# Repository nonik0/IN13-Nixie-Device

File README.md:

# IN13 Nixie Device

## Overview

This Nixie project is a continutation of the same spirit of most of my earlier Nixie projects: take an existing Nixie device, house it in a clean, well-built metal case, and maybe do a few addtions or modifications along the way. For me, the magic of Nixie tubes lies in their soft, ghostly glow—subtle, warm, and inviting. A simple, high-quality enclosure helps keep the attention where it belongs: on the Nixie itself.

Over the years, I’ve owned a few different Nixie thermometers, but they all came in acrylic cases. Aside from being acrylic, they were also bulky compared to the slim IN-13 tube and also used LED edge-lit acrylic to indicate temperature ranges. I don’t hate edge-lit acrylic on principle, but pairing that aesthetic with the aesthetic of Nixie tubes feels like a cardinal sin to me. I know there’s a huge market for flashy Nixie clocks with rainbow LEDs and effects, and plenty of people enjoy that style, but it’s just not for me. In my house, there’s a Nixie device in every room—and not a single RGB LED in sight. That’s been a personal rule for a while now.

At some point while browsing other Nixie projects, my mental levee broke and I had to start this project. TODO prototype? I started by finding a case I liked and sized well with an IN-13 tube, and worked back from that. My challenge for this was creating relatively cramped single sided PCB custom made for the case I had chosen, and this project is the result! and I dove into building this. I started by picking out a metal case I liked that fit the IN-13 well, and worked backward from there. My main challenge for this project was designing a compact, single-sided PCB tailored specifically to the dimensions of the enclosure I had chosen, and what you see here is the result!

inspiration:
https://yager.io/vumeter/vu.html
https://www.tindie.com/products/eclipsevl/in-13-bargraph-nixie-tube-with-driver-and-dc-dc/

## Hardware
The hardware is designed in KiCad 8.0, and all design files are included in the [hardware/kicad8.0](hardware/kicad8.0) directory.

The main hardware components are:
- IN-13 Nixie Tube
- [Bud Industries Aluminum Enclosure](https://www.budind.com/product/nema-ip-rated-boxes/an-a-series-style-a-aluminum-enclosure/an-1311-2)
- ESP32-C6 Mini
- TODO

## Firmware

TODO

## Images

TODO

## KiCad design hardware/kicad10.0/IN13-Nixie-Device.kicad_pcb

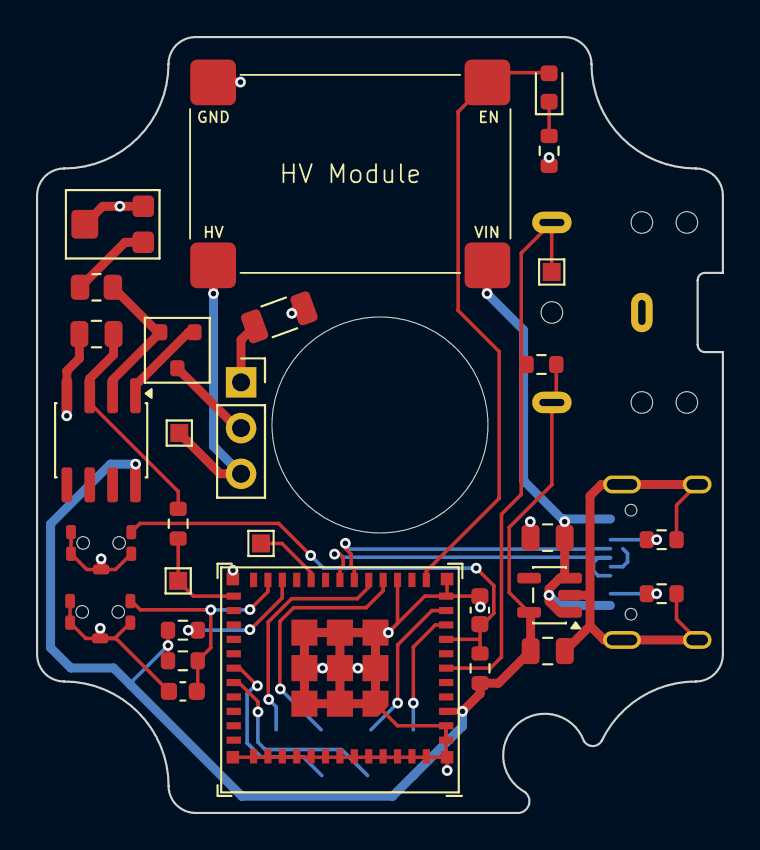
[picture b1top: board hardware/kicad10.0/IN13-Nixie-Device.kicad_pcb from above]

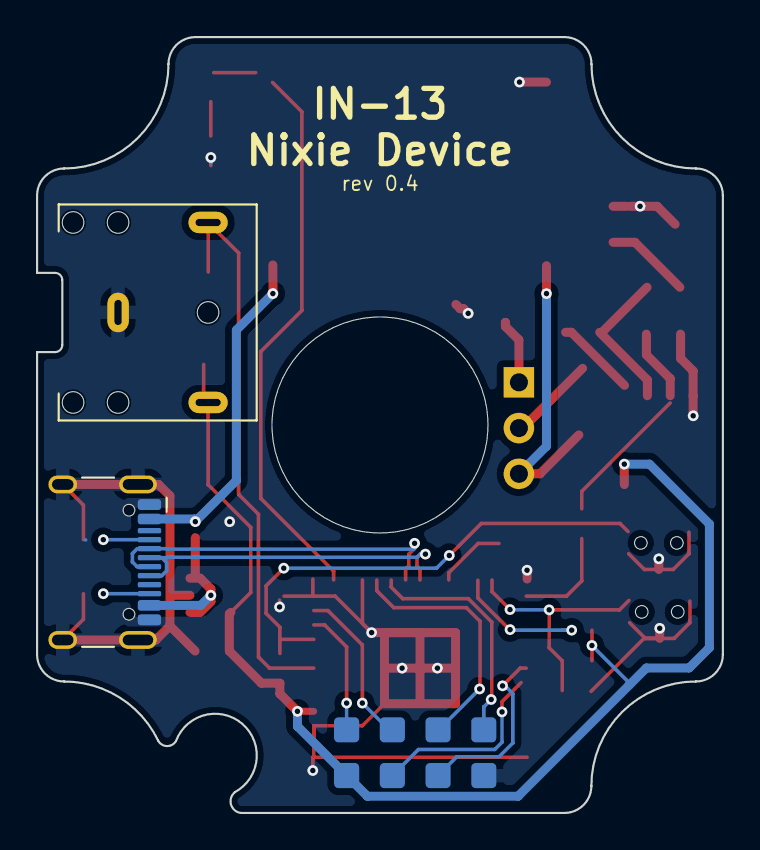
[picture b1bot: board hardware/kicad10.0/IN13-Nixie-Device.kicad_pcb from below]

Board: 2 copper layers, 38.1 x 43.1 mm, 33 parts (4 on the bottom side), 28 nets.

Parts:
C2: 100nF; C_0805_2012Metric
C3, C4: 1u; C_0603_1608Metric
C9, C12: 22u; C_0805_2012Metric
D3: LED; LED_0603_1608Metric
J1: PINHD_1x3_Female; PinSocket_1x03_P2.54mm_Vertical
J2: AudioJack3; Jack_3.5mm_CUI_SJ1-3523N_Horizontal_NoEdgeSilkscreen
J3: USB_C_Receptacle_USB2.0_16P; USB_C_Receptacle_HCTL_HC-TYPE-C-16P-01A
J4, J5: PINHD_1x4_Male; Pads_1x4_2.54mm
Q1: MMBTA42; SOT-23
R1: 220k; R_1206_3216Metric
R2, R3, R5, R6, R11: 10k; R_0603_1608Metric
R4: 330; R_0805_2012Metric
R12, R13: 5.1K; R_0603_1608Metric
R14: 220; R_0603_1608Metric
RV1: 2k; Potentiometer_Bourns_TC33X_Vertical
SW1, SW2: SW_Push; Mitsumi_SOFSeries_SMD_Button
TP1, TP2, TP4, TP5: TestPoint; TestPoint_Pad_1.0x1.0mm
U1: LM358; SOIC-8_3.9x4.9mm_P1.27mm
U2: ESP32-C6-MINI-1/U; ESP32-C6-MINI-1U
U4: AP2112K-3.3; SOT-23-5
U11: HV Module; AliExpress_HV_Module

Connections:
+3.3V: C12.1, J2.T, J4.1, R2.1, R5.2, R6.2, R11.1, U1.8 (V+), U2.3 (3V3), U4.5 (VOUT)
BOOT: C4.1, R6.1, SW2.1 (A), U2.23 (GPIO9)
D+: J3.A6 (D+), J3.B6 (D+), U2.18 (GPIO13/USB_D+)
D-: J3.A7 (D-), J3.B7 (D-), U2.17 (GPIO12/USB_D-)
EN: C3.1, R2.2, SW1.1 (A), U2.8 (EN/CHIP_PU)
GND: C2.2, C3.2, C4.2, C9.2, C12.2, J2.S, J3.A1 (GND), J3.A12 (GND), J3.B1 (GND), J3.B12 (GND), J3.SH (SHIELD), J4.4, R1.1, R12.2, R13.2, R14.1, RV1.2, RV1.3, SW1.2 (B), SW1.3 (GND), SW2.2 (B), SW2.3 (GND), U1.4 (V-), U2.1 (GND), U2.2 (GND), U2.11 (GND), U2.14 (GND), U2.36 (GND), U2.37 (GND), U2.38 (GND), U2.39 (GND), U2.40 (GND), U2.41 (GND), U2.42 (GND), U2.43 (GND), U2.44 (GND), U2.45 (GND), U2.46 (GND), U2.47 (GND), U2.48 (GND), U2.49 (GND), U2.50 (GND), U2.51 (GND), U2.52 (GND), U2.53 (GND), U4.2 (GND), U11.3 (Gnd)
HV: J1.3, TP2.1, U11.4 (Vout)
HVEN: D3.2 (A), U2.12 (GPIO0/ADC1_CH0/XTAL_32K_P), U11.2 (EN)
unnamed: D3.1 (K), R14.2
unnamed: J1.1, R1.2
unnamed: J3.A5 (CC1), R12.1
unnamed: J3.B5 (CC2), R13.1
unnamed: Q1.1 (B), U1.1
unnamed: J1.2, Q1.3 (C)
unnamed: Q1.2 (E), R4.1, U1.2 (-)
unnamed: R4.2, RV1.1
unnamed: C2.1, R3.1, U1.3 (+)
unnamed: R5.1, U2.22 (GPIO8)
unnamed: TP5.1 (1_1), U2.20 (GPIO15)
PWM: R3.2, TP1.1 (1_1), U2.25 (GPIO19)
RX: J4.3, U2.30 (U0RXD/GPIO17)
SIGNAL: J2.R, R11.2, TP4.1 (1_1), U2.6 (GPIO3/ADC1_CH3)
TCK: J5.3, U2.15 (MTCK/GPIO6/ADC1_CH6)
TDI: J5.2, U2.10 (MTDI/GPIO5/ADC1_CH5)
TDO: J5.4, U2.16 (MTDO/GPIO7)
TMS: J5.1, U2.9 (MTMS/GPIO4/ADC1_CH4)
TX: J4.2, U2.31 (U0TXD/GPIO16)
VBUS: C9.1, J3.A4 (VBUS), J3.A9 (VBUS), J3.B4 (VBUS), J3.B9 (VBUS), U4.1 (VIN), U4.3 (EN), U11.1 (Vin)

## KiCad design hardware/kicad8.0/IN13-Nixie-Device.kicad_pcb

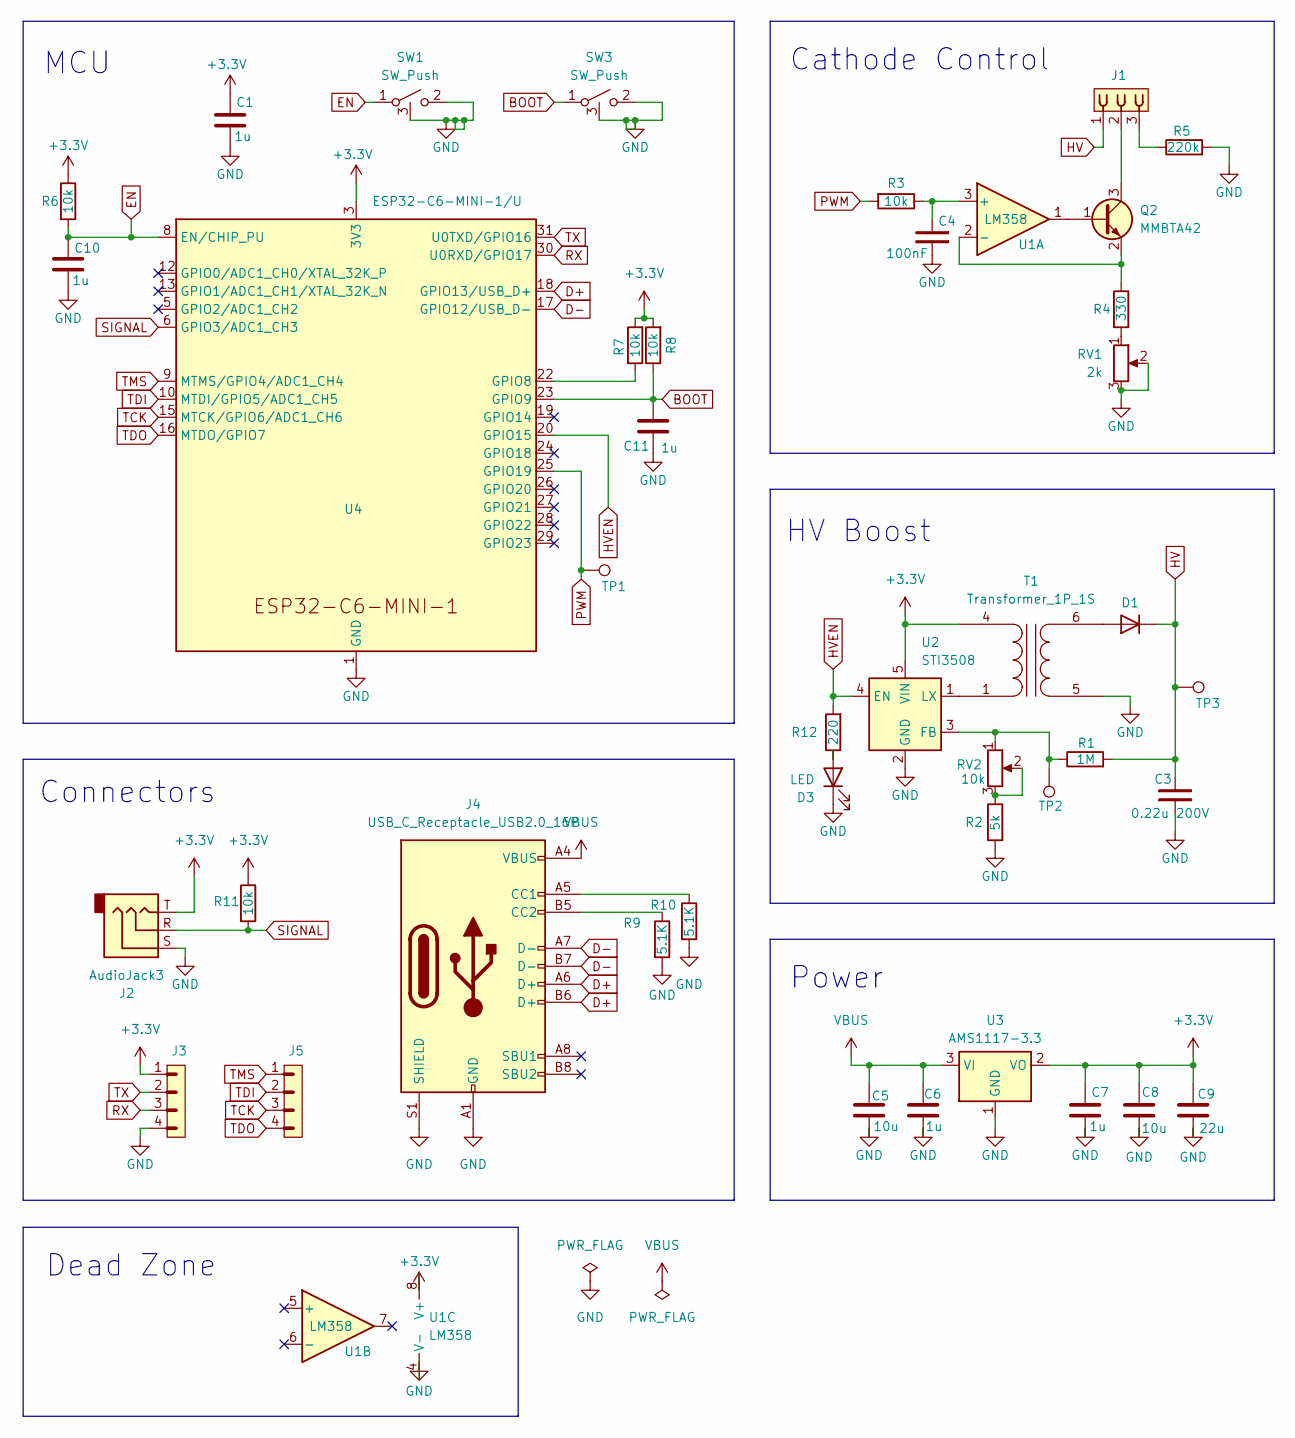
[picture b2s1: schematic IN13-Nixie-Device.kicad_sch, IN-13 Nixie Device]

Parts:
C1, C10, C11: 1u; C_0603_1608Metric
C3: 0.22u 200V; C_1210_3225Metric
C4: 100nF; C_0805_2012Metric
C5, C8: 10u; C_0805_2012Metric
C6, C7: 1u; C_0805_2012Metric
C9: 22u; C_0805_2012Metric
D1: US1G; D_SMA
D3: LED; LED_0603_1608Metric
J1: PINHD_1x3_Female; PinSocket_1x03_P2.54mm_Vertical
J2: AudioJack3; Jack_3.5mm_CUI_SJ1-3523N_Horizontal_NoEdgeSilkscreen
J3, J5: PINHD_1x4_Male; Pads_1x4_2.54mm
J4: USB_C_Receptacle_USB2.0_16P; USB_C_Receptacle_HCTL_HC-TYPE-C-16P-01A
Q2: MMBTA42; SOT-23
R1: 1M; R_0805_2012Metric
R2: 5k; R_0805_2012Metric
R3, R6, R7, R8, R11: 10k; R_0603_1608Metric
R4: 330; R_0805_2012Metric
R5: 220k; R_1206_3216Metric
R9, R10: 5.1K; R_0603_1608Metric
R12: 220; R_0603_1608Metric
RV1: 2k; Potentiometer_Bourns_TC33X_Vertical
RV2: 10k; Potentiometer_Bourns_TC33X_Vertical
SW1, SW3: SW_Push; Mitsumi_SOFSeries_SMD_Button
T1: Transformer_1P_1S; EE0504S
TP1, TP2, TP3: TestPoint; TestPoint_Pad_1.0x1.0mm
U1: LM358; SOIC-8_3.9x4.9mm_P1.27mm
U2: STI3508; SOT-23-6
U3: AMS1117-3.3; SOT-223-3_TabPin2
U4: ESP32-C6-MINI-1/U; ESP32-C6-MINI-1U

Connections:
+3.3V: C1.1, C7.1, C8.1, C9.1, J2.T, J3.1, R6.1, R7.2, R8.2, R11.1, T1.4 (AA), U1.8 (V+), U2.5 (VIN), U3.2 (VO), U4.3 (3V3)
BOOT: C11.1, R8.1, SW3.1 (A), U4.23 (GPIO9)
D+: J4.A6 (D+), J4.B6 (D+), U4.18 (GPIO13/USB_D+)
D-: J4.A7 (D-), J4.B7 (D-), U4.17 (GPIO12/USB_D-)
EN: C10.1, R6.2, SW1.1 (A), U4.8 (EN/CHIP_PU)
GND: C1.2, C3.1, C4.2, C5.2, C6.2, C7.2, C8.2, C9.2, C10.2, C11.2, D3.1 (K), J2.S, J3.4, J4.A1 (GND), J4.A12 (GND), J4.B1 (GND), J4.B12 (GND), J4.S1 (SHIELD), R2.2, R5.2, R9.2, R10.2, RV1.2, RV1.3, SW1.2 (B), SW1.3 (GND), SW3.2 (B), SW3.3 (GND), T1.5 (SA), U1.4 (V-), U2.2 (GND), U3.1 (GND), U4.1 (GND), U4.2 (GND), U4.11 (GND), U4.14 (GND), U4.36 (GND), U4.37 (GND), U4.38 (GND), U4.39 (GND), U4.40 (GND), U4.41 (GND), U4.42 (GND), U4.43 (GND), U4.44 (GND), U4.45 (GND), U4.46 (GND), U4.47 (GND), U4.48 (GND), U4.49 (GND), U4.50 (GND), U4.51 (GND), U4.52 (GND), U4.53 (GND)
HV: C3.2, D1.1 (K), J1.1, R1.2, TP3.1
HVEN: R12.2, U2.4 (EN), U4.20 (GPIO15)
unnamed: D1.2 (A), T1.6 (SB)
unnamed: D3.2 (A), R12.1
unnamed: J1.3, R5.1
unnamed: J4.A5 (CC1), R10.1
unnamed: J4.B5 (CC2), R9.1
unnamed: Q2.1 (B), U1.1
unnamed: J1.2, Q2.3 (C)
unnamed: Q2.2 (E), R4.1, U1.2 (-)
unnamed: R2.1, RV2.2, RV2.3
unnamed: R4.2, RV1.1
unnamed: T1.1 (AB), U2.1 (LX)
unnamed: C4.1, R3.1, U1.3 (+)
unnamed: R1.1, RV2.1, TP2.1, U2.3 (FB)
unnamed: R7.1, U4.22 (GPIO8)
PWM: R3.2, TP1.1, U4.25 (GPIO19)
RX: J3.3, U4.30 (U0RXD/GPIO17)
SIGNAL: J2.R, R11.2, U4.6 (GPIO3/ADC1_CH3)
TCK: J5.3, U4.15 (MTCK/GPIO6/ADC1_CH6)
TDI: J5.2, U4.10 (MTDI/GPIO5/ADC1_CH5)
TDO: J5.4, U4.16 (MTDO/GPIO7)
TMS: J5.1, U4.9 (MTMS/GPIO4/ADC1_CH4)
TX: J3.2, U4.31 (U0TXD/GPIO16)
VBUS: C5.1, C6.1, J4.A4 (VBUS), J4.A9 (VBUS), J4.B4 (VBUS), J4.B9 (VBUS), U3.3 (VI)

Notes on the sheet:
Cathode Control
HV Boost
Dead Zone
MCU
Connectors
Power

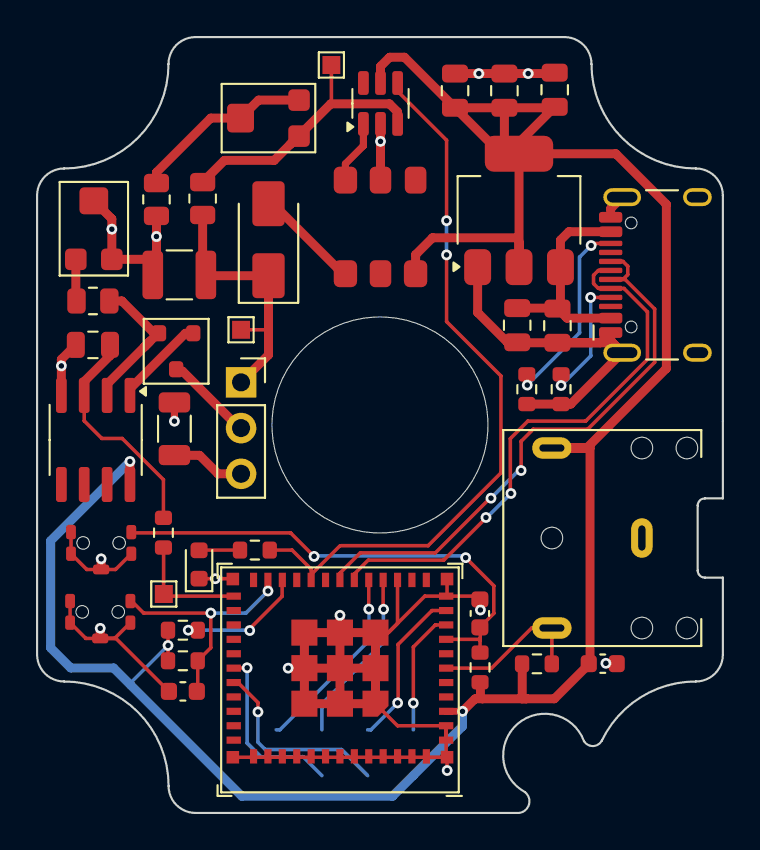
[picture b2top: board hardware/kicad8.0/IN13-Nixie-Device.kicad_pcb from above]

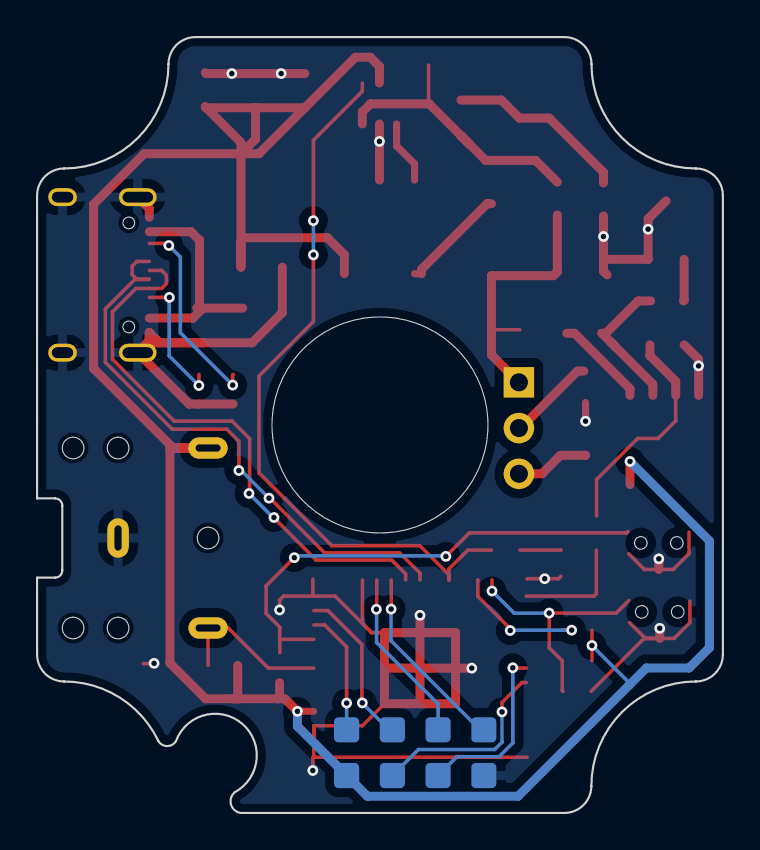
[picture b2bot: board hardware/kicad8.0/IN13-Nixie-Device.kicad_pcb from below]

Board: 2 copper layers, 38.1 x 43.1 mm, 42 parts (2 on the bottom side), 31 nets.

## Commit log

2025-02-07 initial commit, schematic in progress
2025-02-10 minor
2025-03-01 adding boilerplate rust esp project
2025-03-01 finished basic schematic
2025-03-03 starting pwm
2025-03-03 cathode control and temperature tasks
2025-03-03 temp to control
2025-03-04 improve task comms, control HV enable
2025-03-05 pin updates
2025-03-07 pcb edge cut
2025-03-09 esp32c6 module
2025-03-11 gave up and did cpp impl fast
2025-03-11 in progress stuff
2025-03-11 rest updates
2025-03-11 cleanup and fixes
2025-03-23 progress
2025-03-24 layout progress, kicad proj rename
2025-03-26 starting traces
2025-04-07 layout passing DRC (except USB conn)
2025-04-07 usb line adjust
2025-04-15 final board revisions and images
2025-05-05 skeleton README
2025-07-08 pcb revision
2025-09-19 pcb revision, improve boost circuit
2026-04-11 pivot to hv module, kicad 10.0
2026-04-11 schematic fixes
2026-04-11 schematic and layour rework start
2026-04-13 revision passing DRC
2026-04-14 final rev 0.4
